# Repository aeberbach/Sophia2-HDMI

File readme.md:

This is the HDMI output PCB that I designed to replace the DVI daughterboard supplied with the amazing [Sophia 2 by Simius](https://forums.atariage.com/topic/307175-sophia-2-improved-gtia-replacement/#comment-4544874)

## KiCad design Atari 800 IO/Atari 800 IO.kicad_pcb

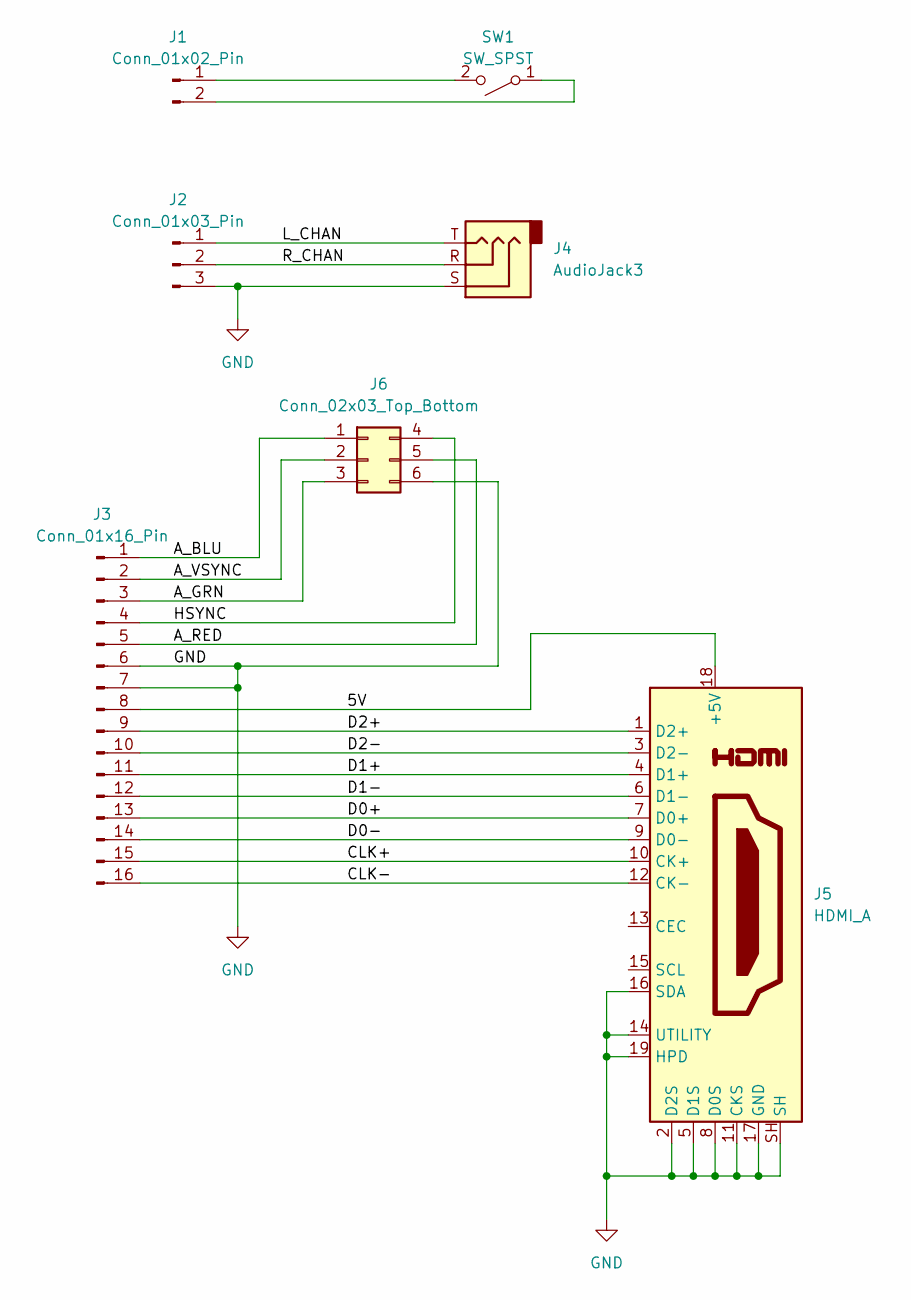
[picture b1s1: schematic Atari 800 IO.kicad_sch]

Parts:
J1: Conn_01x02_Pin; JST_XH_B2B-XH-AM_1x02_P2.50mm_Vertical
J2: Conn_01x03_Pin; JST_XH_B3B-XH-A_1x03_P2.50mm_Vertical
J3: Conn_01x16_Pin; TE_Micro-MaTch_1-215079-6_2x08_P1.27mm_Vertical
J4: AudioJack3; xess-KYCON-STX-3000
J5: HDMI_A; HDMI_A_Molex_208658-1001_Horizontal
J6: Conn_02x03_Top_Bottom; IDC-Header_2x03_P2.54mm_Vertical
SW1: SW_SPST; SW_Tactile_SPST_Angled_PTS645Vx83-2LFS

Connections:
/5V: J3.8, J5.18 (+5V)
/A_BLU: J3.1, J6.1
/A_GRN: J3.3, J6.3
/A_RED: J3.5, J6.5
/A_VSYNC: J3.2, J6.2
/CLK+: J3.15, J5.10 (CK+)
/CLK-: J3.16, J5.12 (CK-)
/D0+: J3.13, J5.7 (D0+)
/D0-: J3.14, J5.9 (D0-)
/D1+: J3.11, J5.4 (D1+)
/D1-: J3.12, J5.6 (D1-)
/D2+: J3.9, J5.1 (D2+)
/D2-: J3.10, J5.3 (D2-)
/HSYNC: J3.4, J6.4
/L_CHAN: J2.1, J4.T
/R_CHAN: J2.2, J4.R
GND: J2.3, J3.6, J3.7, J4.S, J5.2 (D2S), J5.5 (D1S), J5.8 (D0S), J5.11 (CKS), J5.14 (UTILITY), J5.16 (SDA), J5.17 (GND), J5.19 (HPD), J5.SH, J6.6
unnamed: J1.1, SW1.2 (B)
unnamed: J1.2, SW1.1 (A)

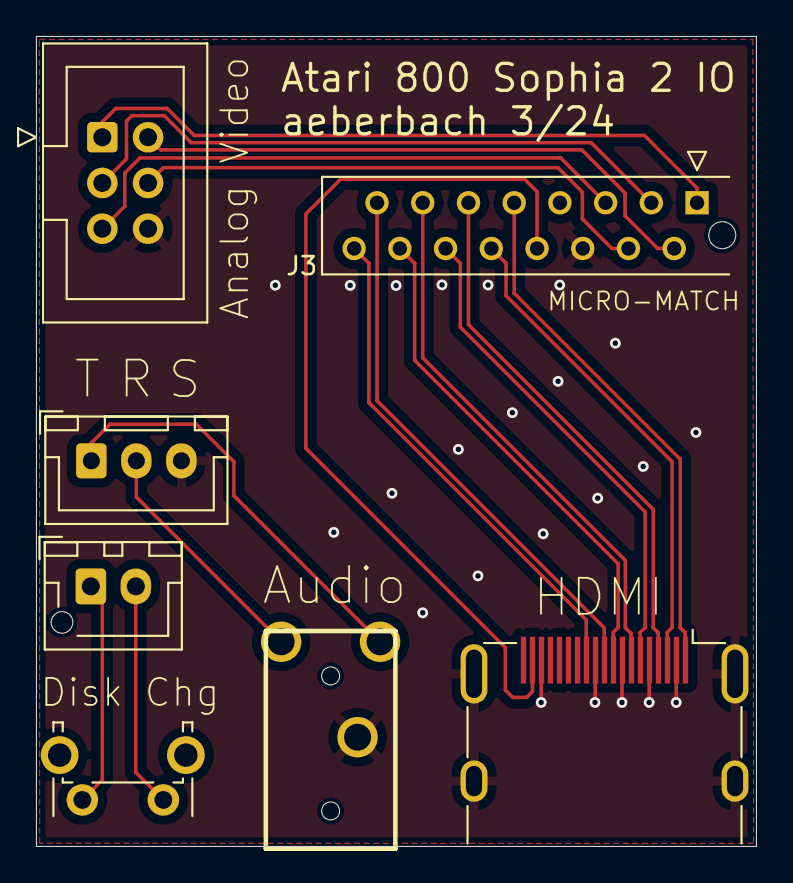
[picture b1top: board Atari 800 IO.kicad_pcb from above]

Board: 2 copper layers, 40.0 x 45.0 mm, 7 parts (0 on the bottom side), 19 nets.

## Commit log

2024-05-06 Add project to repo for sharing
2024-05-06 readme and picture
2024-05-06 fix markdown
